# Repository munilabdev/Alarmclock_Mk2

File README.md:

# Alarmclock_Mk2
Second prototype of my adhan- and alarmclock

## What is the Alarmclock_Mk2?
The Alarmclock_Mk2 is the second prototype of a self-designed alarmclock, which shows the time and date, the next prayertime, and plays the Adhan and a alarm, if the time has come.

I used an ESP32 as the microcontroller, a MAX98357A as the amplifier, a 1.3" OLED, a SD-module and a rotary-encoder for input.

Available are code and pcb-files made in KiCad, available to use via MIT License. 

There are still some flaws, for example bouncing of the rotary-encoder, which are intended to be adressed in Mk3, which will be started soon.

I would be glad about feedback and criticism.

Thank you.

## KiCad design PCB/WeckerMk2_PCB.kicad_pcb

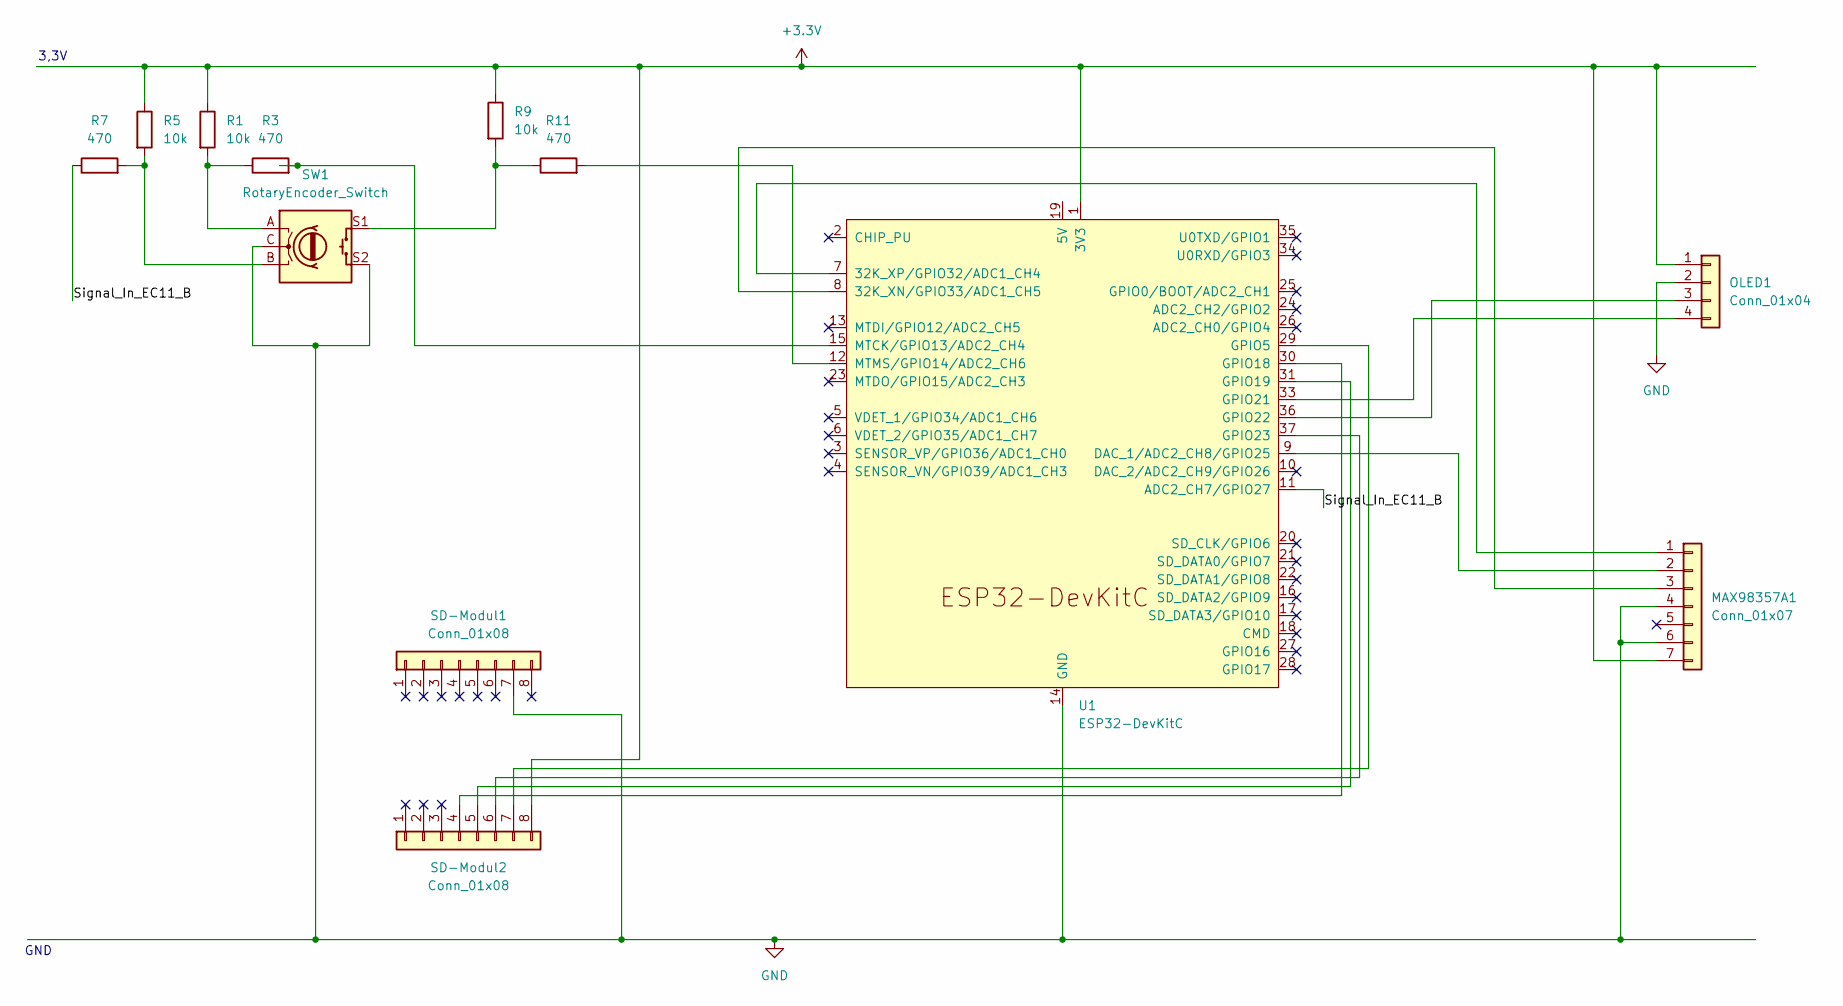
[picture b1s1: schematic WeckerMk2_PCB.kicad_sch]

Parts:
MAX98357A1: Conn_01x07; PinHeader_1x07_P2.00mm_Horizontal
OLED1: Conn_01x04; PinHeader_1x04_P2.00mm_Horizontal
R1, R5, R9: 10k; R_Axial_DIN0207_L6.3mm_D2.5mm_P10.16mm_Horizontal
R3, R7, R11: 470; R_Axial_DIN0207_L6.3mm_D2.5mm_P10.16mm_Horizontal
SD-Modul1, SD-Modul2: Conn_01x08; PinHeader_1x08_P2.00mm_Horizontal
SW1: RotaryEncoder_Switch; RotaryEncoder_Alps_EC11E-Switch_Vertical_H20mm
U1: ESP32-DevKitC

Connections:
+3.3V: MAX98357A1.7, OLED1.1, R1.1, R5.1, R9.1, SD-Modul2.8, U1.1 (3V3)
/Signal_In_EC11_B: R7.1, U1.11 (ADC2_CH7/GPIO27)
GND: MAX98357A1.4, MAX98357A1.6, OLED1.2, SD-Modul1.7 (Pin_7_7), SW1.C, SW1.S2, U1.14 (GND), U1.32 (GND), U1.38 (GND)
unnamed: MAX98357A1.1, U1.7 (32K_XP/GPIO32/ADC1_CH4)
unnamed: MAX98357A1.2, U1.9 (DAC_1/ADC2_CH8/GPIO25)
unnamed: MAX98357A1.3, U1.8 (32K_XN/GPIO33/ADC1_CH5)
unnamed: OLED1.3, U1.36 (GPIO22)
unnamed: OLED1.4, U1.33 (GPIO21)
unnamed: R1.2, R3.1, SW1.A
unnamed: R5.2, R7.2, SW1.B
unnamed: R9.2, R11.1, SW1.S1
unnamed: SD-Modul2.4, U1.30 (GPIO18)
unnamed: SD-Modul2.5, U1.31 (GPIO19)
unnamed: SD-Modul2.6, U1.37 (GPIO23)
unnamed: SD-Modul2.7, U1.29 (GPIO5)
unnamed: R3.2, U1.15 (MTCK/GPIO13/ADC2_CH4)
unnamed: R11.2, U1.12 (MTMS/GPIO14/ADC2_CH6)

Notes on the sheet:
3,3V
GND

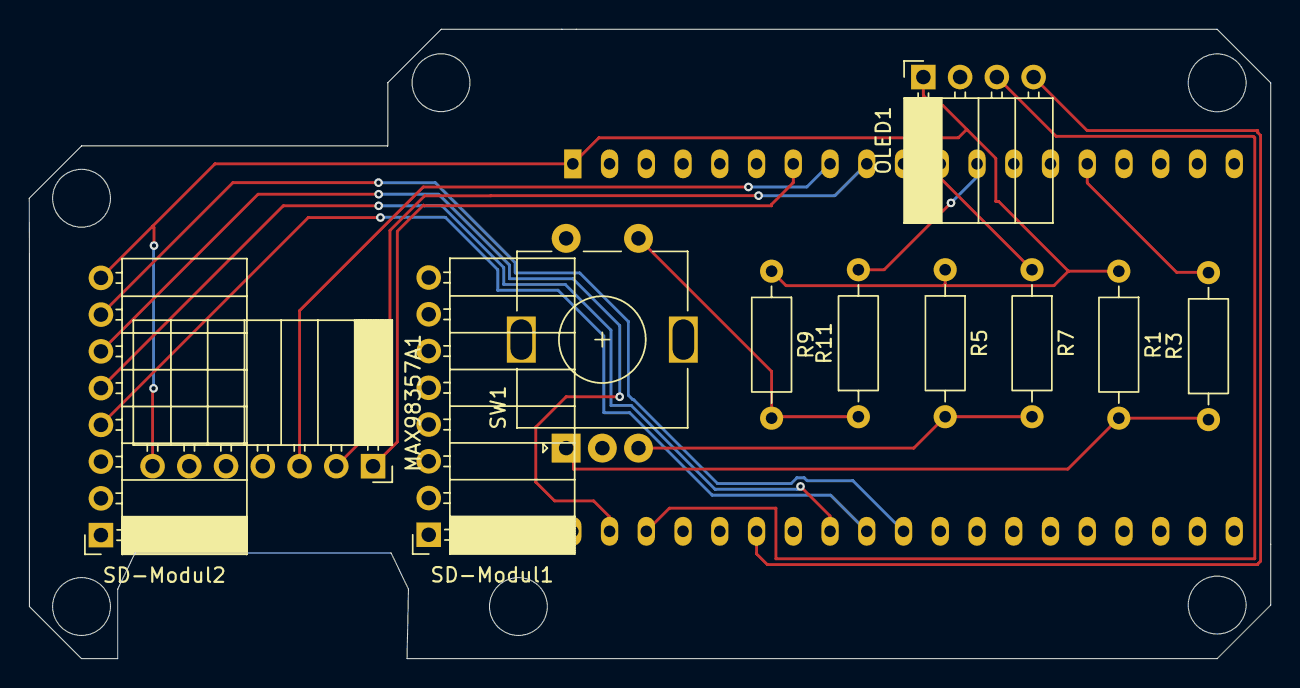
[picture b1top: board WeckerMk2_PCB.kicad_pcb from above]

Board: 2 copper layers, 85.8 x 43.5 mm, 12 parts (1 on the bottom side), 17 nets.
